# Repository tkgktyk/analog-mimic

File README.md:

# Analog Mimic (analog-mimic)

## Overview

Analog Mimic is a drop-in, programmable analog front-end (AFE) module powered by a robust "MCU + DSP" architecture. It is designed to bring software-defined flexibility to physical analog boundaries.

**Key Features:**
* **Versatile Emulation:** Physically mimics diverse analog circuits (e.g., filters, amplifiers, comparators).
* **Instant Reconfiguration:** Fully reconfigurable on the fly with a single I²C command.
* **Drop-in Ready:** Designed to be easily integrated into your existing hardware prototyping workflow.

## Why This Exists

Learning analog circuits requires three separate competencies: designing a
circuit, building it, and evaluating how it behaves. These are serial — a
learner must succeed at all three before observing any behaviour at all.
Failures at the build stage are frequently unrelated to understanding:
a cold solder joint, a misread colour code, stray capacitance on a
breadboard. The learner receives no feedback about the circuit, only about
their assembly technique.

Circuit simulators remove this barrier, but replace physical signals with
screen output. The learner never connects a probe, never sees noise, never
observes what happens when a real source drives a real load.

Analog Mimic decouples evaluation from design and construction while keeping
the signals physical. A learner connects a probe to a real output, observes a
real waveform on a real oscilloscope, and drives real downstream circuitry —
without first designing or building the emulated circuit. Changing the
emulated topology or its parameters is an I²C write from a host
microcontroller, so a single board covers filters, comparators, rectifiers,
and non-linear blocks. Comparing a Sallen-Key response against a Schmitt
trigger becomes a parameter change rather than a rewiring exercise.

Because reconfiguration is driven from the digital side, the module also
provides an entry path for learners who arrived through Arduino-style digital
prototyping and have not yet worked with analog signal chains.

## Hardware Concept
* **Form Factor:** Pmod-style 6-pin connector with a compact footprint (35.56 mm × 20 mm). SCL, SDA, GND and VCC follow the Pmod Type 6 (I²C) pinout; pins 1 and 2 carry GND and AOUT instead of the optional INT and RESET signals.
* **On-Chip Integration:** Seamless integration of internal operational amplifier-based input/output buffers, anti-aliasing filters (AAF), and anti-imaging filters (AIF) mapped directly alongside the high-speed processing core.

```mermaid
graph LR
    classDef plain fill:none,stroke:none,color:#000,font-weight:bold;
    classDef mcu fill:#f9f9f9,stroke:#333,stroke-width:1px;

    AIN(AIN):::plain
    AOUT(AOUT):::plain

    AIN --> ADC
    
    %% Subgraph for MCU
    subgraph PY32F071[PY32F071]
        ADC[Buffer/AAF/ADC]
        DSP[DSP<br>Analog emulator]
        DAC[DAC/AIF]
        
        ADC --> DSP --> DAC
    end

    DAC --> AOUT

    style PY32F071 fill:#e6f2ff,stroke:#0066cc,stroke-width:2px,stroke-dasharray:5 5
```

### I²C Address
Two solder jumpers on the bottom side select the address (read at power-up).

| A1 | A0 | Address |
|---|---|---|
| open | open | 0x40 |
| open | closed | 0x41 |
| closed | open | 0x42 |
| closed | closed | 0x43 |

## Software Ecosystem
To lower the barrier to entry for real-time digital signal processing, we provide a dedicated **C++ library for Arduino**. 
* **Zero-Hassle Control:** Fixed-point arithmetic and low-level I²C register maps are completely abstracted away.
* **Intuitive High-Level API:** Users can dynamically switch emulation modes and fine-tune physical parameters—such as cutoff frequencies, amplifier gains, or envelope release times—by simply passing variables into straightforward function calls.

*For details on the inner workings and the register map, see [firmware_reference.md](docs/firmware_reference.md). The Arduino library is [AnalogMimic](https://github.com/tkgktyk/analog-mimic-arduino).*

## DEMO: Analog Emulation

## Reproducing the Measurements in the Manuscript

This firmware accompanies a manuscript on output timing determinism,
prepared for submission to IEEJ Transactions on Electronics, Information
and Systems. The device and the signal chain described in Sect. 3 of that
manuscript correspond to the `mimic01` board in this repository.

### Toolchain

* Arm GNU Toolchain 15.2.Rel1 (`arm-none-eabi-gcc` 15.2.1 20251203)
* GNU Make

All commands below are issued from `firmware/targets/mimic0x/`. If the
toolchain is not on `PATH`, pass its location explicitly:

    make GCC_PATH="/path/to/arm-gnu-toolchain/bin"

### Issuing agent (build-time)

The agent that writes the output register is selected at compile time
through `ENGINE`, which defines `MIMIC_ENGINE_DMA` or `MIMIC_ENGINE_CPU`.

| Agent | Normal service | Measurement build      |
|-------|----------------|------------------------|
| DMA   | `make`         | `make dac`             |
| CPU   | `make cpu`     | `make ENGINE=CPU dac`  |

Each build writes to its own tree under `build/`, so the four coexist:
`MIMIC01`, `MIMIC01_cpu`, `MIMIC01_dacpulse`, `MIMIC01_cpu_dacpulse`.

Note that `ENGINE` must be given on the command line when combined with
`dac`. The `cpu` target sets `ENGINE` only for its own recursive
invocation, so `make cpu dac` builds the DMA variant.

### Output route (run-time)

The route is **not** a build option. The host selects the analog route
(DAC + AIF) or the digital route (GPIO) over I²C as part of a
reconfiguration, together with the topology and the coefficients. The four
rows of Table 1 are therefore two builds, each exercised on both routes.

### Measurement build

The distributions of Sect. 4 were taken with `ENABLE_DAC_PULSE`, a toggle
that overrides the emulated output so that every period carries a
transition of known polarity. A firmware built without it emulates the
selected circuit as usual and will not reproduce Fig. 4 and Fig. 5.

### Dependency

`firmware/lib/PY32F071_Firmware` is
[OpenPuya/PY32F071_Firmware](https://github.com/OpenPuya/PY32F071_Firmware)
v1.0.5 (`73e384cd`), distributed under BSD-3-Clause. It is included as a
git submodule; clone with git clone --recursive
(or run git submodule update --init).

### Host side

The host is not included here. It only issues I²C writes to
select the emulation mode, the output route, and the coefficients. The
register map is defined in `firmware/core/Inc/mimic_registers.h`, which is
the authoritative description of the interface; any I²C master will do.

The measurements of Sect. 4 were taken with an Arduino host performing a
single reconfiguration before each acquisition: a second-order biquad
filter on the analog route, and a comparator mode on the digital route.

## Open Source Hardware Certification

Analog Mimic is certified as open source hardware by the [Open Source Hardware Association (OSHWA)](https://certification.oshwa.org/).
Each hardware revision is certified separately; firmware updates do not change the board revision or its certification.

| Board | OSHWA UID | Certified | Hardware files | Notes |
|-------|-----------|-----------|----------------|-------|
| Mimic 01 | [JP000025](https://certification.oshwa.org/jp000025.html) | 2026-10-29 | [`hardware/assembly/mimic01_20260522/`](hardware/assembly/mimic01_20260522/) | Initial release |

Licenses: hardware under CERN-OHL-S-2.0, firmware under GPL-3.0-only, documentation under CC BY 4.0. See [LICENSE](LICENSE) for details.

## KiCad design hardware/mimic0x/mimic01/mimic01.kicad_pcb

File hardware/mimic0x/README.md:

## How these files were generated
KiCad 9.0.7 + "Fabrication Toolkit" plugin (v5.3.0), default settings. No manual post-processing was required; the plugin emits Gerber X2, drill files, BOM (LCSC part numbers) and CPL with JLCPCB-compatible rotation/origin conventions.

## Order specification (reference: JLCPCB)

| Parameter | Value |
|---|---|
| Board size | 35.56 × 20.0 mm * Converted into 35.6 x 20.0 mm Automatically |
| Layers | 2 |
| Thickness | 1.6 mm |
| Copper weight | 1 oz |
| Surface finish | HASL(lead-free) |
| Solder mask / silkscreen | white / black |
| Min track/spacing | 0.2/0.2 mm |
| Min hole size | 0.3 mm |
| Assembly | 1 side (top) |
| Tooling holes | added by JLCPCB |
| Panelization | none (single) |
| Parts source | JLCPCB Assembly Parts Library |

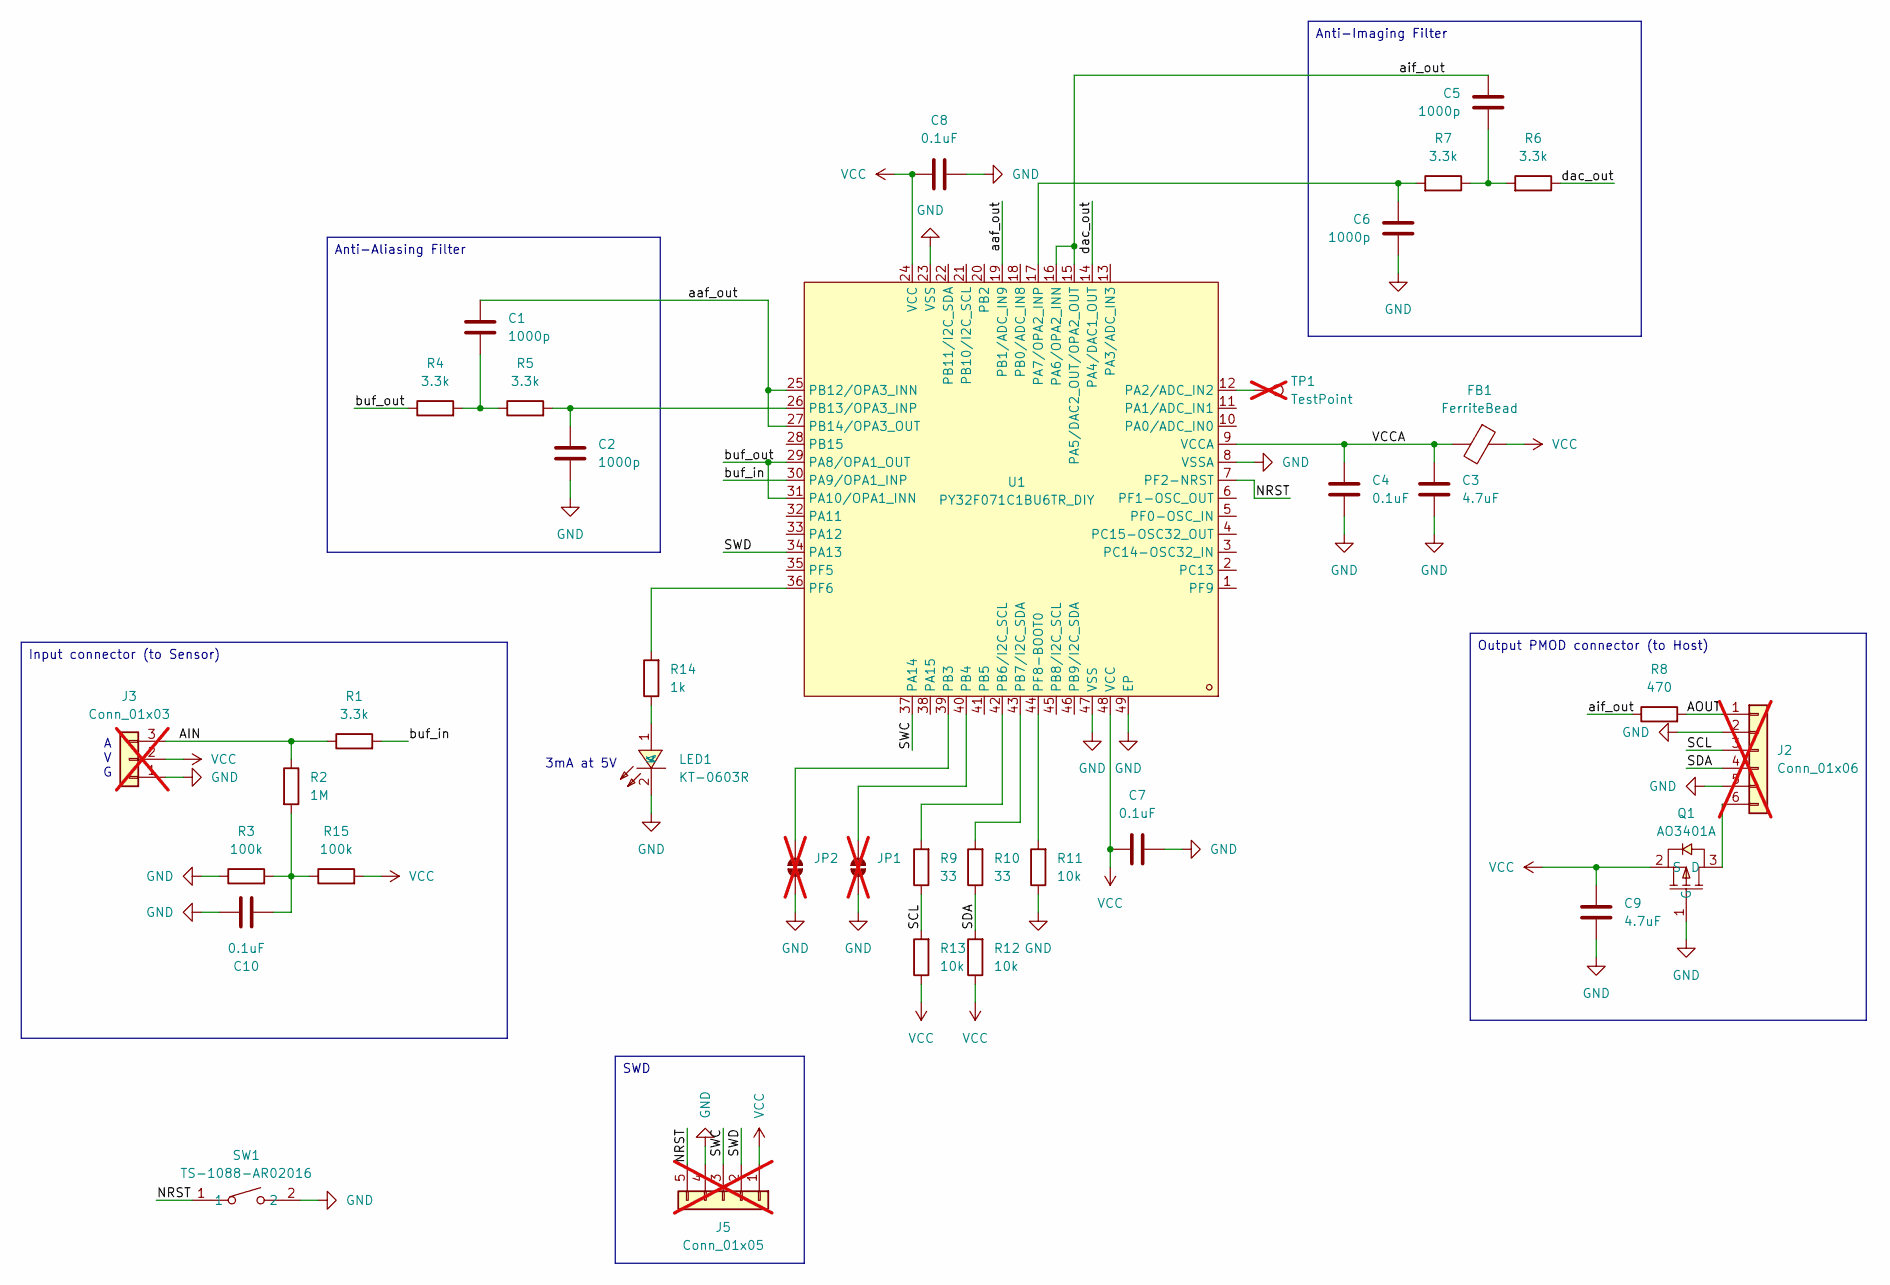
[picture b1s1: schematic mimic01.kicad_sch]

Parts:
C1, C2, C5, C6: 1000p; C_0402_1005Metric; LCSC Part C53547
C3, C9: 4.7uF; C_0603_1608Metric; LCSC Part C19666
C4, C7, C8, C10: 0.1uF; C_0402_1005Metric; LCSC Part C1525
FB1: FerriteBead; L_0603_1608Metric; LCSC Part C1002
J2: Conn_01x06; PinHeader_1x06_P2.54mm_Horizontal_DIY; not fitted
J3: Conn_01x03; PinHeader_1x03_P2.54mm_Horizontal_DIY; not fitted
J5: Conn_01x05; PinSocket_1x05_P2.54mm_Vertical_DIY; not fitted
JP1, JP2: SolderJumper_2_Open; SolderJumper-2_P1.3mm_Open_TrianglePad1.0x1.5mm; not fitted
LED1: KT-0603R; LED-SMD_L1.6-W0.8-R-RD; MPN KT-0603R; LCSC Part C2286
Q1: AO3401A; SOT-23_L2.9-W1.3-P1.90-LS2.4-BR; MPN AO3401A; LCSC Part C15127
R1, R4, R5, R6: 3.3k; R_0402_1005Metric; LCSC Part C25890
R2: 1M; R_0402_1005Metric; LCSC Part C26083
R3, R15: 100k; R_0402_1005Metric; LCSC Part C25741
R7: 3.3k; R_0603_1608Metric; LCSC Part C22978
R8: 470; R_0402_1005Metric; LCSC Part C25117
R9, R10: 33; R_0402_1005Metric; LCSC Part C25105
R11, R12, R13: 10k; R_0402_1005Metric; LCSC Part C25744
R14: 1k; R_0402_1005Metric; LCSC Part C11702
SW1: TS-1088-AR02016; SW-SMD_L3.9-W3.0-P4.45; MPN TS-1088-AR02016; LCSC Part C720477
TP1: TestPoint; TestPoint_Pad_D1.5mm; not fitted
U1: PY32F071C1BU6TR_DIY; VQFN-48_L6.0-W6.0-P0.40-TL-EP4.4; LCSC Part C7434410

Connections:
/AIN: J3.3, R1.1, R2.1
/AOUT: J2.1, R8.2
/NRST: J5.5, SW1.1, U1.7 (PF2-NRST)
/SCL: J2.3, R9.1, R13.2
/SDA: J2.4, R10.1, R12.2
/SWC: J5.3, U1.37 (PA14)
/SWD: J5.2, U1.34 (PA13)
/VCCA: C3.1, C4.1, FB1.2, U1.9 (VCCA)
/aaf_out: C1.1, U1.19 (PB1/ADC_IN9), U1.25 (PB12/OPA3_INN), U1.27 (PB14/OPA3_OUT)
/aif_out: C5.1, R8.1, U1.15 (PA5/DAC2_OUT/OPA2_OUT), U1.16 (PA6/OPA2_INN)
/buf_in: R1.2, U1.30 (PA9/OPA1_INP)
/buf_out: R4.1, U1.29 (PA8/OPA1_OUT), U1.31 (PA10/OPA1_INN)
/dac_out: R6.1, U1.14 (PA4/DAC1_OUT)
GND: C2.2, C3.2, C4.2, C6.2, C7.2, C8.2, C9.2, C10.2, J2.2, J2.5, J3.1, J5.4, JP1.1 (A), JP2.1 (A), LED1.2 (K), Q1.1 (G), R3.1, R11.1, SW1.2, U1.8 (VSSA), U1.23 (VSS), U1.47 (VSS), U1.49 (EP)
unnamed: C1.2, R4.2, R5.1
unnamed: C5.2, R6.2, R7.1
unnamed: C10.1, R2.2, R3.2, R15.1
unnamed: J2.6, Q1.3 (D)
unnamed: JP1.2 (B), U1.40 (PB4)
unnamed: JP2.2 (B), U1.39 (PB3)
unnamed: LED1.1 (A), R14.1
unnamed: TP1.1 (1_1), U1.12 (PA2/ADC_IN2)
unnamed: C6.1, R7.2, U1.17 (PA7/OPA2_INP)
unnamed: R9.2, U1.42 (PB6/I2C_SCL)
unnamed: R10.2, U1.43 (PB7/I2C_SDA)
unnamed: C2.1, R5.2, U1.26 (PB13/OPA3_INP)
unnamed: R14.2, U1.36 (PF6)
unnamed: R11.2, U1.44 (PF8-BOOT0)
VCC: C7.1, C8.1, C9.1, FB1.1, J3.2, J5.1, Q1.2 (S), R12.1, R13.1, R15.2, U1.24 (VCC), U1.48 (VCC)

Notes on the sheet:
3mA at 5V
A V G
Input connector (to Sensor)
SWD
Output PMOD connector (to Host)
Anti-Imaging Filter
Anti-Aliasing Filter

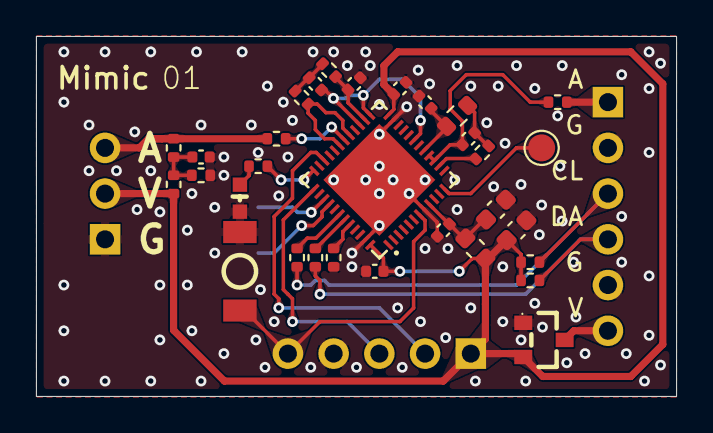
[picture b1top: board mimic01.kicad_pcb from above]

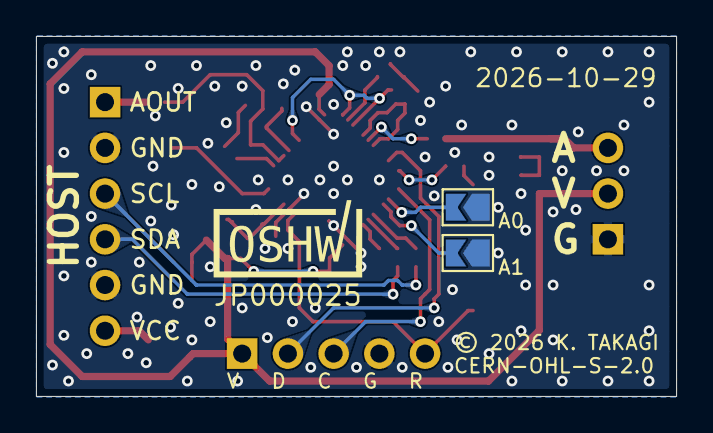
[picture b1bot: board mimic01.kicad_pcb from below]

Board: 2 copper layers, 35.6 x 20.0 mm, 36 parts (2 on the bottom side), 29 nets.

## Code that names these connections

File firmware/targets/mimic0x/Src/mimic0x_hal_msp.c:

/**
 ******************************************************************************
 * @file    mimic0x_hal_msp.c
 * @author  TAKAGI Katsuyuki
 * @brief   MCU Support Package (MSP) Implementation for Base-Model Hardware, 
 * Handling Low-Level Peripheral Clock, GPIO, and NVIC Initializations.
 *-----------------------------------------------------------------------------
 * Copyright (C) 2026 TAKAGI Katsuyuki
 *
 * This program is free software: you can redistribute it and/or modify
 * it under the terms of the GNU General Public License as published by
 * the Free Software Foundation, version 3.
 *
 * This program is distributed in the hope that it will be useful,
 * but WITHOUT ANY WARRANTY; without even the implied warranty of
 * MERCHANTABILITY or FITNESS FOR A PARTICULAR PURPOSE.  See the
 * GNU General Public License for more details.
 *
 * You should have received a copy of the GNU General Public License
 * along with this program.  If not, see <https://www.gnu.org/licenses/>.
 ******************************************************************************
 */

#include "mimic0x_msp.h"
#include "py32f0xx_hal.h"

/* ==================================================================== */
/* Hardware Revision Pin Definitions (mimic00)                          */
/* ==================================================================== */

#if defined(TARGET_MIMIC00)
  // I2C Peripheral Configuration Pins (PB6 / PB7)
  #define I2C_SCL_PORT      GPIOB
  #define I2C_SCL_PIN       GPIO_PIN_6
  #define I2C_SCL_AF        GPIO_AF1_I2C1 

  #define I2C_SDA_PORT      GPIOB
  #define I2C_SDA_PIN       GPIO_PIN_7
  #define I2C_SDA_AF        GPIO_AF1_I2C1

  // OPA1 Pins (Input Buffer)
  #define OPA1_INP_PIN      GPIO_PIN_9    // PA9
  #define OPA1_INN_PIN      GPIO_PIN_10   // PA10
  #define OPA1_OUT_PIN      GPIO_PIN_8    // PA8
  #define OPA1_PORT         GPIOA

  // OPA2 Pins (Output Driver / DAC2)
  #define OPA2_INP_PIN      GPIO_PIN_7    // PA7
  #define OPA2_INN_PIN      GPIO_PIN_6    // PA6
  #define OPA2_OUT_PIN      GPIO_PIN_5    // PA5
  #define OPA2_PORT         GPIOA

  // OPA3 Pins (Anti-Aliasing Filter)
  #define OPA3_INP_PIN      GPIO_PIN_13   // PB13
  #define OPA3_INN_PIN      GPIO_PIN_12   // PB12
  #define OPA3_OUT_PIN      GPIO_PIN_14   // PB14
  #define OPA3_PORT         GPIOB

  // ADC & DAC Pins
  #define ADC_IN9_PIN       GPIO_PIN_1    // PB1 (Reads AAF Out)
  #define ADC_IN9_PORT      GPIOB
  #define DAC1_OUT_PIN      GPIO_PIN_4    // PA4
  #define DAC_PORT          GPIOA
#elif defined(TARGET_MIMIC01)
  // I2C Peripheral Configuration Pins (PB6 / PB7)
  #define I2C_SCL_PORT      GPIOB
  #define I2C_SCL_PIN       GPIO_PIN_6
  #define I2C_SCL_AF        GPIO_AF1_I2C1 

  #define I2C_SDA_PORT      GPIOB
  #define I2C_SDA_PIN       GPIO_PIN_7
  #define I2C_SDA_AF        GPIO_AF1_I2C1

  // OPA1 Pins (Input Buffer)
  #define OPA1_INP_PIN      GPIO_PIN_9    // PA9
  #define OPA1_INN_PIN      GPIO_PIN_10   // PA10
  #define OPA1_OUT_PIN      GPIO_PIN_8    // PA8
  #define OPA1_PORT         GPIOA

  // OPA2 Pins (Output Driver / DAC2)
  #define OPA2_INP_PIN      GPIO_PIN_7    // PA7
  #define OPA2_INN_PIN      GPIO_PIN_6    // PA6
  #define OPA2_OUT_PIN      GPIO_PIN_5    // PA5
  #define OPA2_PORT         GPIOA

  // OPA3 Pins (Anti-Aliasing Filter)
  #define OPA3_INP_PIN      GPIO_PIN_13   // PB13
  #define OPA3_INN_PIN      GPIO_PIN_12   // PB12
  #define OPA3_OUT_PIN      GPIO_PIN_14   // PB14
  #define OPA3_PORT         GPIOB

  // ADC & DAC Pins
  #define ADC_IN9_PIN       GPIO_PIN_1    // PB1 (Reads AAF Out)
  #define ADC_IN9_PORT      GPIOB
  #define DAC1_OUT_PIN      GPIO_PIN_4    // PA4
  #define DAC_PORT          GPIOA
#else
  #error "Hardware revision macro is not defined! Please define HW_REV_MIMIC00 in your build configuration."
#endif

/* ==================================================================== */
/* Interrupt Priority Definitions                                       */
/* ==================================================================== */
#define I2C_IRQ_PRIORITY    1
#define ADC_IRQ_PRIORITY    0

/* ==================================================================== */
/* System Initialization                                                */
/* ==================================================================== */
void HAL_MspInit(void)
{
  __HAL_RCC_SYSCFG_CLK_ENABLE();
  __HAL_RCC_PWR_CLK_ENABLE();
}

/* ==================================================================== */
/* Analog Initialization (OPA, ADC, DAC)                                */
/* ==================================================================== */
void HAL_OPA_MspInit(OPA_HandleTypeDef *hopa)
{
  GPIO_InitTypeDef GPIO_InitStruct = {0};

  /* Enable GPIO Clocks */
  __HAL_RCC_GPIOA_CLK_ENABLE();
  __HAL_RCC_GPIOB_CLK_ENABLE();

  /* Enable OPA peripheral clock */
  __HAL_RCC_OPA_CLK_ENABLE();

  /* All Analog pins must be set to GPIO_MODE_ANALOG */
  GPIO_InitStruct.Mode  = GPIO_MODE_ANALOG;
  GPIO_InitStruct.Pull  = GPIO_NOPULL;

  switch(hopa->Init.Part) {
    case OPA1:
      GPIO_InitStruct.Pin = OPA1_INP_PIN | OPA1_INN_PIN | OPA1_OUT_PIN;
      HAL_GPIO_Init(OPA1_PORT, &GPIO_InitStruct);
      break;
    case OPA2:
      GPIO_InitStruct.Pin = OPA2_INP_PIN | OPA2_INN_PIN | OPA2_OUT_PIN;
      HAL_GPIO_Init(OPA2_PORT, &GPIO_InitStruct);
      break;
    case OPA3:
      GPIO_InitStruct.Pin = OPA3_INP_PIN | OPA3_INN_PIN | OPA3_OUT_PIN;
      HAL_GPIO_Init(OPA3_PORT, &GPIO_InitStruct);
      break;
    default:
      break;
  }
}

void HAL_ADC_MspInit(ADC_HandleTypeDef *hadc)
{
  GPIO_InitTypeDef GPIO_InitStruct = {0};

  if(hadc->Instance == ADC1)
  {
    __HAL_RCC_ADC_CONFIG(RCC_ADCCLKSOURCE_PCLK_DIV4);

    __HAL_RCC_GPIOB_CLK_ENABLE();
    __HAL_RCC_ADC_CLK_ENABLE();

    GPIO_InitStruct.Pin  = ADC_IN9_PIN;
    GPIO_InitStruct.Mode = GPIO_MODE_ANALOG;
    GPIO_InitStruct.Pull = GPIO_NOPULL;
    HAL_GPIO_Init(ADC_IN9_PORT, &GPIO_InitStruct);

    HAL_NVIC_SetPriority(ADC_COMP_IRQn, ADC_IRQ_PRIORITY, 0); 
    HAL_NVIC_EnableIRQ(ADC_COMP_IRQn);
  }
}

void HAL_DAC_MspInit(DAC_HandleTypeDef *hdac)
{
  GPIO_InitTypeDef GPIO_InitStruct = {0};

  if(hdac->Instance == DAC1)
  {
    __HAL_RCC_GPIOA_CLK_ENABLE();
    __HAL_RCC_DAC1_CLK_ENABLE();

    // Initialize DAC1_OUT (PA4) 
    GPIO_InitStruct.Pin  = DAC1_OUT_PIN;
    GPIO_InitStruct.Mode = GPIO_MODE_ANALOG;
    GPIO_InitStruct.Pull = GPIO_NOPULL;
    HAL_GPIO_Init(DAC_PORT, &GPIO_InitStruct);
  }
}

/* ==================================================================== */
/* Timer Initialization (TIM3)                                          */
/* ==================================================================== */
void HAL_TIM_Base_MspInit(TIM_HandleTypeDef *htim_base)
{
  if(htim_base->Instance == TIM3)
  {
    /* Enable TIM3 peripheral clock */
    __HAL_RCC_TIM3_CLK_ENABLE();
  }
}

/**
 * @brief  Initializes the low-level hardware resources for I2C1.
 * Note: Since I2C1 uses the LL driver, this function is NOT called 
 * automatically by HAL and must be invoked manually in main.c.
 */
void I2C1_Hardware_Init(void)
{
  GPIO_InitTypeDef GPIO_InitStruct = {0};

  /* 1. Enable peripheral clocks */
  __HAL_RCC_I2C1_CLK_ENABLE();
  __HAL_RCC_GPIOB_CLK_ENABLE();

  /* 2. Initialize GPIO (PB6=SCL, PB7=SDA) */
  GPIO_InitStruct.Pin = I2C_SCL_PIN | I2C_SDA_PIN;
  GPIO_InitStruct.Mode = GPIO_MODE_AF_OD;
  GPIO_InitStruct.Pull = GPIO_NOPULL;
  GPIO_InitStruct.Speed = GPIO_SPEED_FREQ_HIGH;
  GPIO_InitStruct.Alternate = I2C_SCL_AF;
  HAL_GPIO_Init(I2C_SCL_PORT, &GPIO_InitStruct);

  /* 3. Configure NVIC for I2C1 */
  HAL_NVIC_SetPriority(I2C1_IRQn, 1, 0); 
  HAL_NVIC_EnableIRQ(I2C1_IRQn);

  /* 4. Force reset the I2C1 module to clear any hanging states */
  __HAL_RCC_I2C1_FORCE_RESET();
  __HAL_RCC_I2C1_RELEASE_RESET();
}

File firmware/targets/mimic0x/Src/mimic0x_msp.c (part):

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/* ==================================================================== */

#if defined(TARGET_MIMIC00) || defined(TARGET_MIMIC01)
  // I2C Peripheral Configuration Pins (PB6 / PB7)
  #define I2C_SCL_PORT      GPIOB
  #define I2C_SCL_PIN       GPIO_PIN_6
  #define I2C_SCL_AF        GPIO_AF1_I2C1 
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  #define I2C_SDA_AF        GPIO_AF1_I2C1

  // OPA1 Pins (Input Buffer)
  #define OPA1_INP_PIN      GPIO_PIN_9    // PA9
  #define OPA1_INN_PIN      GPIO_PIN_10   // PA10
  #define OPA1_OUT_PIN      GPIO_PIN_8    // PA8
  #define OPA1_PORT         GPIOA

  // OPA3 Pins (Anti-Aliasing Filter)
  #define OPA3_INP_PIN      GPIO_PIN_13   // PB13
  #define OPA3_INN_PIN      GPIO_PIN_12   // PB12
  #define OPA3_OUT_PIN      GPIO_PIN_14   // PB14
  #define OPA3_PORT         GPIOB

  // ADC & DAC Pins
  #define ADC_IN9_PIN       GPIO_PIN_1    // PB1 (Reads AAF Out)
  #define ADC_IN9_PORT      GPIOB
  #define DAC1_OUT_PIN      GPIO_PIN_4    // PA4
  #define DAC_PORT          GPIOA

  #if defined(TARGET_MIMIC01)
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    
    // I2C address jumpers (closed = GND, internal pull-ups)
    #define ADDR_JP_PORT      GPIOB
    #define ADDR_A0_PIN       GPIO_PIN_3    // PB3 -> address bit 0
    #define ADDR_A1_PIN       GPIO_PIN_4    // PB4 -> address bit 1

  #endif
#else
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    }
    HAL_TIM_OC_Start(&htim2, TIM_CHANNEL_2);

    // CH3: Reference edge for PA2
    sConfigOC.Pulse = 100;
    if (HAL_TIM_OC_ConfigChannel(&htim2, &sConfigOC, TIM_CHANNEL_3) != HAL_OK) {
        Mimic_HW_ErrorTrap();
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
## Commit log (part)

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2026-05-22 Add datasheet PDF
2026-05-22 Add hybrid open-source licenses (CERN-OHL-S, GPLv3, MIT)
2026-05-22 Update silk and component values
2026-05-28 Add gain/offset calibraion, and decimation feature. Reduced the sampling rate to 192 kHz.
2026-05-29 Add MIMIC_REG_CMD_PORT. Fix the flash protcol, and the main loop.
2026-05-29 Encapsulate mimic_device
2026-05-29 efactor: organize dependencies
2026-05-29 Move unused public function to local
2026-05-30 refactor: clean up and reorganize codebase
2026-05-30 Add: a script to generate Arduino libraries Delete: unnecessary .gitignore
2026-05-30 Add: symbolic link to mimic_registers.h
2026-05-30 Remove actual file
2026-05-30 Add symbolic link
2026-05-30 remove abs path link
2026-05-30 Add relpath symbolic link
2026-05-30 Move: actual mimic_registers.h to software
2026-05-30 move: mimic_registers.h
2026-05-30 delete: mimic_registers.h from software
2026-05-30 Split arduino library (software) into analog-mimic-arduino
2026-05-30 Remove: the description of software
2026-05-30 refactor: makefile
2026-05-30 refactor: split hardware definition into msp
2026-05-30 rename: mimic0x_hal_msp to mimic0x_msp
2026-05-30 rename: mimic0x_hal_msp.c to mimic0x_msp.c
2026-05-30 Add: Ready-LED and test pad for Mimic01 only
2026-05-30 remove asset folder
2026-06-02 Add board and pinout images
    Updated images in README and added new board image.
2026-06-02 Add block diagram of Analog Mimic
2026-06-02 link: relocate .ramfunc section to SRAM via .data section
2026-06-02 Add: debug mode to toggle DAC output
2026-06-02 Add static_assert to prevent phase-shift jitter from odd sampling periods due to 2-phase AHB bus misalignment
2026-06-03 Add demo
2026-06-26 Add reference manual
2026-06-26 Separate dac build from release
2026-06-26 refactoring
2026-06-26 Add a gurad on decimation update

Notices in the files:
README.md:
Open source licenses: Hardware CERN-OHL-S-2.0, Software GPL-3.0-only, Documentation CC-BY-4.0
hardware/mimic0x/mimic01/mimic01.kicad_pcb:
License: CERN-OHL-S-2.0
© 2026 K. TAKAGI
CERN-OHL-S-2.0
